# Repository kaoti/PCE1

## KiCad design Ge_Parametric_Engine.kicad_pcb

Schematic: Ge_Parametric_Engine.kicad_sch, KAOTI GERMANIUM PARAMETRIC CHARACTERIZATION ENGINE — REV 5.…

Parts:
BZ1: BUZZER_12MM; Buzzer_12mm
C1: 100uF_16V; CP_Radial_D8_P3.5mm
C2, C8, C9, C10, C11, C12, C13, C14, C15, C16, C18, C19, C20, C21, C22: 100nF; C_Disc_P5.00mm
C7, C17: 10uF_25V; CP_Radial_D8_P3.5mm
C_A0, C_A1, C_A2, C_A3: 100nF_C0G; C_Disc_P5.00mm
C_A1A, C_A2A: 100uF_16V; CP_Radial_D8_P3.5mm
C_A1B, C_A2B: 100nF; C_Disc_P5.00mm
C_ADC_FA: 10uF_16V; CP_Radial_D8_P3.5mm
C_BAT_BYP: 100uF_16V; CP_Radial_D8_P3.5mm
C_BYP_ISO1, C_BYP_ISO2: 100nF; C_Disc_P5.00mm
C_DAC1, C_DAC2: 100nF; C_Disc_P5.00mm
C_DB_BA: 100nF; C_Disc_P5.00mm
C_DB_BB: 100nF; C_Disc_P5.00mm
C_DB_DN: 100nF; C_Disc_P5.00mm
C_DB_ENCA: 10nF; C_Disc_P5.00mm
C_DB_ENCB: 10nF; C_Disc_P5.00mm
C_DB_ENCSW: 100nF; C_Disc_P5.00mm
C_DB_LF: 100nF; C_Disc_P5.00mm
C_DB_RT: 100nF; C_Disc_P5.00mm
C_DB_UP: 100nF; C_Disc_P5.00mm
C_DIG1: 100uF_16V; CP_Radial_D8_P3.5mm
C_DIG2: 100nF; C_Disc_P5.00mm
C_PI1A, C_PI2A: 100uF_35V; CP_Radial_D8_P3.5mm
C_PI1B, C_PI2B: 100nF; C_Disc_P5.00mm
C_PMID: 10uF_25V; CP_Radial_D8_P3.5mm
C_POR: 1uF; C_Disc_P5.00mm
C_RST_M11: 100nF; C_Disc_P5.00mm
C_SNUB: 10nF; C_Disc_P5.00mm
C_SYS1: 100uF_16V; CP_Radial_D8_P3.5mm
C_SYS2: 100nF; C_Disc_P5.00mm
C_TRES: 1uF; C_Disc_P5.00mm
C_USB_IN: 100nF; C_Disc_P5.00mm
D1: ANA_9V_ON; LED_D3mm_Green
D2: AFE_ACT; LED_D3mm_Blue
D_BZ: 1N4148; D_DO-35_P7.62mm
D_CH1, D_CH2, D_CH3: 1N3595; D_DO-35_P7.62mm
D_CL1, D_CL2, D_CL3: 1N3595; D_DO-35_P7.62mm
D_HVH: 1N3595; D_DO-35_P7.62mm
D_HVL: 1N3595; D_DO-35_P7.62mm
D_LED1: 1_PWR_GREEN; LED_D3mm_Green
D_LED2: 2_CHG_AMBER; LED_D3mm_Yellow
D_LED3: 3_STBY_RF_CYAN; LED_D3mm_Blue
D_LED4: 4_SCAN_BLUE; LED_D3mm_Blue
D_LED5: 5_DUT_OK_GREEN; LED_D3mm_Green
D_LED6: 6_FAULT_RED; LED_D3mm_Red
D_OVP: 1N4743A_13V; D_DO-41_P10.16mm
D_TVS_USB: P6KE15A; D_DO-15_P10.16mm
ENC1: EC11_NAV_KNOB; EC11_Knob_Encoder
F1: RXEF017_170mA; Fuse_PTC_P5.00mm
F_USB: RXEF175_1.75A; Fuse_PTC_P5.00mm
JP_M1_3V3: JP_M1_3V3_ISO; Header_1x02_P2.54mm
JP_M2_3V3: JP_M2_3V3_ISO; Header_1x02_P2.54mm
J_BAT: LIPO_1S_3V7_NON_HV; Header_1x02_P2.54mm
J_CYD_UART: CYD_P1_UART_TAP; Header_1x04_P2.54mm
J_DUT3: DUT_3PIN_SKT; Socket_1x03_DUT
J_KELVIN: KELVIN_LEADS; Header_1x04_P2.54mm
J_NTC: BAT_NTC_10K; Header_1x02_P2.54mm
J_TEMP: DS18B20_TEMP; Socket_TO92_3Pin
J_TERM5: PROBE_5P_508; TerminalBlock_5Pin_508
J_USB_C: USBC_5V_3A_HVDCP; Socket_USBC_Breakout
J_ZIF: ZIF-14_DUT; Socket_ZIF_14Pin
L1: 100uH_1A; L_Radial_P5.00mm
L2: 47uH_1A; L_Radial_P5.00mm
MOD_ADS: ADS1115_16Bit; Socket_ADS1115_Module
MOD_BOOST: MT3608_14.5V; Socket_MT3608_Boost
MOD_CHG: BQ25895_NVDC_3A; Socket_BQ25895_Charger
MOD_TFT1: TFT1_1.9_IPS_CURVE; Socket_TFT_1_9_Curve
MOD_TFT2: TFT2_1.9_IPS_DMM; Socket_TFT_1_9_DMM
Q_ANA_N: 2N7000; Socket_TO92_3Pin
Q_ANA_SW: NDP6020P; TO-220-3_Vertical
Q_BLK: 2N7000; Socket_TO92_3Pin
Q_BZ: 2N3904; Socket_TO92_3Pin
Q_LIM1, Q_LIM2: 2N3906; Socket_TO92_3Pin
Q_OVC: 2N3904; Socket_TO92_3Pin
Q_REV_BAT: NDP6020P; TO-220-3_Vertical
R_ADC_F: 10R_1%; R_Axial_P7.62mm
R_ALRT: 10k; R_Axial_P7.62mm
R_BLEED_SYS: 10k; R_Axial_P7.62mm
R_BZ_B: 1.0k; R_Axial_P7.62mm
R_BZ_PD: 10k; R_Axial_P7.62mm
R_CC1, R_CC2: 5.1k_1%; R_Axial_P7.62mm
R_CYD_RX: 470R; R_Axial_P7.62mm
R_CYD_TX: 470R; R_Axial_P7.62mm
R_D1A, R_D2A, R_D3A, R_D4A: 1.50k_0.1%; R_Axial_P7.62mm
R_D1B, R_D2B, R_D3B, R_D4B: 499R_0.1%; R_Axial_P7.62mm
R_DAC1, R_DAC2: 10k; R_Axial_P7.62mm
R_DACCS: 10k; R_Axial_P7.62mm
R_DAMP1: 2.2R_0.5W; R_Axial_P7.62mm
R_DAMP2: 1.5R_0.25W; R_Axial_P7.62mm
R_DP1, R_DP2: 100k; R_Axial_P7.62mm
R_EN1, R_EN2, R_EN3: 100k; R_Axial_P7.62mm
R_ESD1, R_ESD2, R_ESD3: 10k; R_Axial_P7.62mm
R_G1A, R_G2A: 34.8k_0.1%; R_Axial_P7.62mm
R_G1B, R_G2B: 10.0k_0.1%; R_Axial_P7.62mm
R_G_ANA: 100R; R_Axial_P7.62mm
R_G_BLK: 100R; R_Axial_P7.62mm
R_G_REV: 1.0k; R_Axial_P7.62mm
R_HV1: 100k_0.1%; R_Axial_P7.62mm
R_HV2: 10.0k_0.1%; R_Axial_P7.62mm
R_IBIAS: 10k; R_Axial_P7.62mm
R_ILIM: 43R_1%; R_Axial_P7.62mm
R_ISO1, R_ISO2, R_ISO3: 10k; R_Axial_P7.62mm
R_KA1, R_KA2, R_KA3: 2.49k_0.1%; R_Axial_P7.62mm
R_KB1, R_KB2, R_KB3: 2.20M_0.1%; R_Axial_P7.62mm
R_KG1, R_KG2, R_KG3: 2.49k_0.1%; R_Axial_P7.62mm
R_LA1, R_LA2, R_LA3: 470R_0.1%; R_Axial_P7.62mm
R_LATCH_PD: 10k; R_Axial_P7.62mm
R_LED1: 3.3k; R_Axial_P7.62mm
R_LED2: 1.0k; R_Axial_P7.62mm
R_LED3, R_LED4, R_LED5, R_LED6: 470R; R_Axial_P7.62mm
R_LED_CHG: 1.5k; R_Axial_P7.62mm
R_LED_ISO1, R_LED_ISO2: 470R_1%; R_Axial_P7.62mm
R_LED_PWR: 1.0k; R_Axial_P7.62mm
R_LG1, R_LG2, R_LG3: 470R_0.1%; R_Axial_P7.62mm
R_MB1, R_MB2, R_MB3: 100k_0.1%; R_Axial_P7.62mm
R_OEN: 10k; R_Axial_P7.62mm
R_OVC_DIV1: 100k; R_Axial_P7.62mm
R_OVC_DIV2: 22k; R_Axial_P7.62mm
R_PD1, R_PD2, R_PD3: 100k; R_Axial_P7.62mm
R_PD_ANA: 100k; R_Axial_P7.62mm
R_PD_BLK: 100k; R_Axial_P7.62mm
R_POR: 10k; R_Axial_P7.62mm
R_PR1, R_PR2, R_PR3: 100R_0.5W_0.1%; R_Axial_P7.62mm
R_PU_BA: 10k; R_Axial_P7.62mm
R_PU_BB: 10k; R_Axial_P7.62mm
R_PU_DN: 10k; R_Axial_P7.62mm
R_PU_ENCA: 10k; R_Axial_P7.62mm
R_PU_ENCB: 10k; R_Axial_P7.62mm
R_PU_ENCSW: 10k; R_Axial_P7.62mm
R_PU_ISO1, R_PU_ISO2: 2.2k; R_Axial_P7.62mm
R_PU_LF: 10k; R_Axial_P7.62mm
R_PU_OVC: 10k; R_Axial_P7.62mm
R_PU_RT: 10k; R_Axial_P7.62mm
R_PU_STBY: 10k; R_Axial_P7.62mm
R_PU_SW: 47k; R_Axial_P7.62mm
R_PU_UP: 10k; R_Axial_P7.62mm
R_RST_M11: 10k; R_Axial_P7.62mm
R_SCL: 4.7k; R_Axial_P7.62mm
R_SDA: 4.7k; R_Axial_P7.62mm
R_SNUB: 100R; R_Axial_P7.62mm
R_STAR: 0R_STAR_BRIDGE; Star_Bridge_0R
R_T1CS, R_T2CS: 10k; R_Axial_P7.62mm
R_TEMP: 4.7k; R_Axial_P7.62mm
R_TRES: 10k; R_Axial_P7.62mm
R_UI_SCL: 4.7k; R_Axial_P7.62mm
R_UI_SDA: 4.7k; R_Axial_P7.62mm
SW_A: BTN_A_SCAN; SW_Tact_12mm_Red
SW_B: BTN_B_BACK; SW_Tact_12mm_Blue
SW_BZ: MUTE_SWITCH; SW_Slide_SPDT_THT
SW_DOWN: DPAD_DOWN; SW_Tact_12mm_Yellow
SW_LEFT: DPAD_LEFT; SW_Tact_12mm_Yellow
SW_PWR: MASTER_PWR_DPDT_3A; SW_Slide_DPDT_THT
SW_RIGHT: DPAD_RIGHT; SW_Tact_12mm_Yellow
SW_STBY: STANDBY_RF_MODE; SW_Slide_SPDT_THT
SW_UP: DPAD_UP; SW_Tact_12mm_Yellow
U1, U2, U3: DG408DJ; Socket_DIP-16_W7.62mm
U4: LMC6484IN; Socket_DIP-14_W7.62mm
U5: TLC2272ACP; Socket_DIP-8_W7.62mm
U6, U7: 74HC595N; Socket_DIP-16_W7.62mm
U8: DG412LDJ; Socket_DIP-16_W7.62mm
U9: MCP4822-E/P; Socket_DIP-8_W7.62mm
U10: DG409DJ; Socket_DIP-16_W7.62mm
U11: MCP23017-E/SP; Socket_DIP-28_W7.62mm
U_ISO1, U_ISO2: H11L1M; Socket_DIP-6_W7.62mm
U_LDO_ANA: MCP1826S-3302E/AB; TO-220-3_Vertical
U_LDO_DIG: MCP1826S-3302E/AB; TO-220-3_Vertical
U_MCU1: WEMOS_LOLIN32_Lite; Socket_Wemos_Lolin32_Lite
U_MCU2: ESP32-C3_SuperMini; Socket_ESP32_C3_SuperMini
U_REG9: L78L09ACZ; Socket_TO92_3Pin
U_REG12: L7812CV; TO-220-3_Vertical

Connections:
+3V3_ADC: C9.1, C_ADC_FA.1 (+), MOD_ADS.1 (VDD), R_ADC_F.2
+3V3_ANA: C1.1 (+), C2.1, C12.1, C13.1, C19.1, C_BYP_ISO2.1, JP_M1_3V3.1, J_TEMP.3 (VDD), R_ADC_F.1, R_ALRT.1, R_DACCS.1, R_LED_ISO1.1, R_OEN.1, R_POR.1, R_PU_ISO2.1, R_PU_OVC.1, R_SCL.1, R_SDA.1, R_TEMP.1, U6.16 (VCC), U7.16 (VCC), U8.12 (VL), U9.1 (VDD), U10.2 (EN), U_ISO2.6 (VCC), U_LDO_ANA.3 (VOUT)
+3V3_DIG: C22.1, C_BYP_ISO1.1, C_DIG1.1 (+), C_DIG2.1, JP_M2_3V3.1, MOD_TFT1.2 (VCC), MOD_TFT2.2 (VCC), R_LED_CHG.1, R_LED_ISO2.1, R_LED_PWR.1, R_PU_BA.1, R_PU_BB.1, R_PU_DN.1, R_PU_ENCA.1, R_PU_ENCB.1, R_PU_ENCSW.1, R_PU_ISO1.1, R_PU_LF.1, R_PU_RT.1, R_PU_STBY.1, R_PU_UP.1, R_RST_M11.1, R_T1CS.1, R_T2CS.1, R_TRES.1, R_UI_SCL.1, R_UI_SDA.1, SW_BZ.3 (B), U11.9 (VDD), U_ISO1.6 (VCC), U_LDO_DIG.3 (VOUT)
+9V_LIM: Q_LIM1.3 (C), R_OVC_DIV2.1, U1.9 (S8), U2.9 (S8), U3.9 (S8), U10.6 (S3A)
+9V_REF: C7.1 (+), C8.1, Q_LIM2.1 (E), R_ILIM.1, R_LED1.1, R_OVC_DIV1.1, U_REG9.1 (OUT)
+12V_A: C10.1, C11.1, C14.1, C15.1, C16.1, C17.1 (+), C18.1, C20.1, C21.1, D_CH1.1 (K), D_CH2.1 (K), D_CH3.1 (K), D_HVH.1 (K), D_OVP.1 (K), F1.2, U1.13 (V+), U2.13 (V+), U3.13 (V+), U4.4 (VDD), U5.8 (VCC), U8.13 (V+), U10.14 (V+), U_REG9.3 (IN)
ADC_CAL: C_A3.1, MOD_ADS.10 (A3), R_D4A.2, R_D4B.1
ADC_TP1: C_A0.1, MOD_ADS.7 (A0), R_D1A.2, R_D1B.1, R_ISO1.1
ADC_TP2: C_A1.1, MOD_ADS.8 (A1), R_D2A.2, R_D2B.1, R_ISO2.1
ADC_TP3: C_A2.1, MOD_ADS.9 (A2), R_D3A.2, R_D3B.1, R_ISO3.1
ADS_ALRT: MOD_ADS.6 (ALRT), R_ALRT.2, U_MCU1.4 (IO34)
AFE_SPI_MOSI: U6.14 (SER), U9.4 (SDI), U_MCU1.10 (IO27)
AFE_SPI_SCK: U6.11 (SRCLK), U7.11 (SRCLK), U9.3 (SCK), U_MCU1.11 (IO14)
AGND: C1.2 (-), C2.2, C7.2 (-), C8.2, C9.2, C10.2, C11.2, C12.2, C13.2, C14.2, C15.2, C16.2, C17.2 (-), C18.2, C19.2, C20.2, C21.2, C_A0.2, C_A1.2, C_A1A.2 (-), C_A1B.2, C_A2.2, C_A2A.2 (-), C_A2B.2, C_A3.2, C_ADC_FA.2 (-), C_BYP_ISO2.2, C_DAC1.2, C_DAC2.2, C_PI1A.2 (-), C_PI1B.2, C_PI2A.2 (-), C_PI2B.2, C_POR.2, D1.1 (K), D2.1 (K), D_CL1.2 (A), D_CL2.2 (A), D_CL3.2 (A), D_HVL.2 (A), D_OVP.2 (A), J_KELVIN.4, J_TEMP.1 (GND), J_TERM5.4 (COM), MOD_ADS.2 (GND), MOD_ADS.5 (ADDR), MOD_BOOST.2 (IN-), MOD_BOOST.4 (OUT-), Q_OVC.1 (E), R_D1B.2, R_D2B.2, R_D3B.2, R_D4B.2, R_DP1.2, R_DP2.2, R_EN1.2, R_EN2.2, R_EN3.2, R_G1B.2, R_G2B.2, R_HV2.2, R_IBIAS.2, R_KG1.2, R_KG2.2, R_KG3.2, R_LATCH_PD.2, R_LG1.2, R_LG2.2, R_LG3.2, R_PD1.2, R_PD2.2, R_PD3.2, R_STAR.2 (AGND), U1.3 (V-), U1.10 (S7), U1.14 (GND), U2.3 (V-), U2.10 (S7), U2.14 (GND), U3.3 (V-), U3.10 (S7), U3.14 (GND), U4.11 (GND), U5.4 (GND), U6.8 (GND), U7.8 (GND), U8.3 (S1), U8.4 (V-), U8.5 (GND), U8.6 (S4), U8.7 (D4), U8.8 (IN4), U8.11 (S3), U8.14 (S2), U9.5 (LDAC), U9.7 (VSS), U10.3 (V-), U10.9 (DB), U10.10 (S4B), U10.11 (S3B), U10.12 (S2B), U10.13 (S1B), U10.15 (GND), U_ISO2.5 (GND), U_LDO_ANA.2 (GND), U_MCU1.13 (GND), U_REG9.2 (GND), U_REG12.2 (GND)
ANA_I2C_SCL: MOD_ADS.3 (SCL), R_SCL.2, U_MCU1.17 (IO23/SCL)
ANA_I2C_SDA: MOD_ADS.4 (SDA), R_SDA.2, U_MCU1.16 (IO19/SDA)
ANA_PWR_EN: R_G_ANA.1, R_PD_ANA.1, U11.8 (GPB7)
BAT_NTC: J_NTC.1, MOD_CHG.6 (TS)
BTN_A: C_DB_BA.1, R_PU_BA.2, SW_A.1, U11.25 (GPA4)
BTN_B: C_DB_BB.1, R_PU_BB.2, SW_B.1, U11.26 (GPA5)
BTN_DOWN: C_DB_DN.1, R_PU_DN.2, SW_DOWN.1, U11.22 (GPA1)
BTN_LEFT: C_DB_LF.1, R_PU_LF.2, SW_LEFT.1, U11.23 (GPA2)
BTN_RIGHT: C_DB_RT.1, R_PU_RT.2, SW_RIGHT.1, U11.24 (GPA3)
BTN_UP: C_DB_UP.1, R_PU_UP.2, SW_UP.1, U11.21 (GPA0)
BUF_CAL: R_D4A.1, U4.13 (4IN-), U4.14 (4OUT)
BUF_TP1: R_D1A.1, U4.1 (1OUT), U4.2 (1IN-)
BUF_TP2: R_D2A.1, U4.6 (2IN-), U4.7 (2OUT)
BUF_TP3: R_D3A.1, U4.8 (3OUT), U4.9 (3IN-)
BZ_COL: BZ1.2 (-), C_SNUB.2, D_BZ.2 (A), Q_BZ.3 (C)
BZ_POS: BZ1.1 (+), D_BZ.1 (K), R_SNUB.1, SW_BZ.2 (COM)
BZ_PWM: R_BZ_B.1, U_MCU2.13 (GPIO3/BZ)
BZ_SNUB_MID: C_SNUB.1, R_SNUB.2
C1_S1: R_LA1.1, U1.4 (S1)
C1_S2: R_KA1.1, U1.5 (S2)
C1_S3: R_MB1.1, U1.6 (S3)
C1_S4: R_KB1.1, U1.7 (S4)
C1_S5: R_LG1.1, U1.12 (S5)
C1_S6: R_KG1.1, U1.11 (S6)
C2_S1: R_LA2.1, U2.4 (S1)
C2_S2: R_KA2.1, U2.5 (S2)
C2_S3: R_MB2.1, U2.6 (S3)
C2_S4: R_KB2.1, U2.7 (S4)
C2_S5: R_LG2.1, U2.12 (S5)
C2_S6: R_KG2.1, U2.11 (S6)
C3_S1: R_LA3.1, U3.4 (S1)
C3_S2: R_KA3.1, U3.5 (S2)
C3_S3: R_MB3.1, U3.6 (S3)
C3_S4: R_KB3.1, U3.7 (S4)
C3_S5: R_LG3.1, U3.12 (S5)
C3_S6: R_KG3.1, U3.11 (S6)
CAL_A0: U10.1 (A0), U_MCU1.6 (IO32)
CAL_A1: U10.16 (A1), U_MCU1.7 (IO33)
CAL_MUX_OUT: U4.12 (4IN+), U10.8 (DA)
CHG_STAT_N: D_LED2.1 (K), MOD_CHG.10 (STAT)
CYD_RX_TAP: J_CYD_UART.4, R_CYD_RX.2
CYD_TX_TAP: J_CYD_UART.3, R_CYD_TX.2
DAC1_FILT: C_DAC1.1, R_DAC1.2, R_DP1.1, U5.3 (1IN+)
DAC1_RAW: R_DAC1.1, U9.8 (VOUTA)
DAC2_FILT: C_DAC2.1, R_DAC2.2, R_DP2.1, U5.5 (2IN+)
DAC2_RAW: R_DAC2.1, U9.6 (VOUTB)
DAC_CS: R_DACCS.2, U9.2 (CS), U_MCU1.9 (DAC2/26)
DGND: C22.2, C_BAT_BYP.2 (-), C_BYP_ISO1.2, C_DB_BA.2, C_DB_BB.2, C_DB_DN.2, C_DB_ENCA.2, C_DB_ENCB.2, C_DB_ENCSW.2, C_DB_LF.2, C_DB_RT.2, C_DB_UP.2, C_DIG1.2 (-), C_DIG2.2, C_PMID.2 (-), C_RST_M11.2, C_SYS1.2 (-), C_SYS2.2, C_TRES.2, C_USB_IN.2, D_LED1.1 (K), D_LED3.1 (K), D_LED4.1 (K), D_LED5.1 (K), D_LED6.1 (K), D_TVS_USB.2 (A), ENC1.2 (C), ENC1.5 (S2), J_BAT.2, J_CYD_UART.2, J_NTC.2, J_USB_C.2 (GND), MOD_CHG.3 (GND), MOD_CHG.11 (CE_N), MOD_CHG.12 (OTG), MOD_TFT1.1 (GND), MOD_TFT2.1 (GND), Q_ANA_N.1 (S), Q_BLK.1 (S), Q_BZ.1 (E), R_BLEED_SYS.2, R_BZ_PD.2, R_CC1.2, R_CC2.2, R_G_REV.2, R_PD_ANA.2, R_PD_BLK.2, R_STAR.1 (DGND), SW_A.2, SW_B.2, SW_DOWN.2, SW_LEFT.2, SW_RIGHT.2, SW_STBY.1 (A), SW_UP.2, U11.10 (VSS), U11.15 (A0), U11.16 (A1), U11.17 (A2), U_ISO1.5 (GND), U_LDO_DIG.2 (GND), U_MCU2.10 (GND)
DMM_30V: J_TERM5.5 (V30V), R_HV1.1
DMM_30V_DIV: D_HVH.2 (A), D_HVL.1 (K), R_HV1.2, R_HV2.1, U10.7 (S4A)
ENC_A: C_DB_ENCA.1, ENC1.1 (A), R_PU_ENCA.2, U11.1 (GPB0)
ENC_B: C_DB_ENCB.1, ENC1.3 (B), R_PU_ENCB.2, U11.2 (GPB1)
ENC_SW: C_DB_ENCSW.1, ENC1.4 (S1), R_PU_ENCSW.2, U11.27 (GPA6)
ESD_TP1: R_ESD1.2, U4.3 (1IN+)
ESD_TP2: R_ESD2.2, U4.5 (2IN+)
ESD_TP3: R_ESD3.2, U4.10 (3IN+)
FAST_TP1: R_ISO1.2, U_MCU1.1 (VP/36)
FAST_TP2: R_ISO2.2, U_MCU1.2 (VN/39)
FAST_TP3: R_ISO3.2, U_MCU1.5 (IO35)
FAULT_OVC_N: Q_OVC.3 (C), R_PU_OVC.2, U_MCU1.8 (DAC1/25)
FB_SRCA: R_G1A.2, R_G1B.1, U5.2 (1IN-)
FB_SRCB: R_G2A.2, R_G2B.1, U5.6 (2IN-)
ISO1_A: R_LED_ISO1.2, U_ISO1.1 (A)
ISO2_A: R_LED_ISO2.2, U_ISO2.1 (A)
J_BAT+: J_BAT.1, SW_PWR.2 (COM1)
LED1_A: D1.2 (A), R_LED1.2
LED2_A: D2.2 (A), R_LED2.2
LED2_DRV: R_LED2.1, U7.7 (QH)
LED3_A: D_LED3.2 (A), R_LED3.2
LED4_A: D_LED4.2 (A), R_LED4.2
LED5_A: D_LED5.2 (A), R_LED5.2
LED6_A: D_LED6.2 (A), R_LED6.2
LED_CHG_A: D_LED2.2 (A), R_LED_CHG.2
LED_DUT_OK: R_LED5.1, U11.5 (GPB4)
LED_FAULT: R_LED6.1, U11.6 (GPB5)
LED_PWR_A: D_LED1.2 (A), R_LED_PWR.2
LED_SCAN: R_LED4.1, U11.4 (GPB3)
LED_STBY_RF: R_LED3.1, U11.3 (GPB2)
LIM_BASE: Q_LIM1.2 (B), Q_LIM2.3 (C), R_IBIAS.1
LIM_SENSE: Q_LIM1.1 (E), Q_LIM2.2 (B), R_ILIM.2
LINK_RX_M1: R_PU_ISO2.2, U_ISO2.4 (VO), U_MCU1.26 (IO13)
LINK_RX_M2: R_CYD_RX.1, R_PU_ISO1.2, U_ISO1.4 (VO), U_MCU2.7 (GPIO20/RX)
LINK_TX_M1: U_ISO1.2 (K), U_MCU1.21 (IO16)
LINK_TX_M2: R_CYD_TX.1, U_ISO2.2 (K), U_MCU2.8 (GPIO21/TX)
M1_3V3: JP_M1_3V3.2, U_MCU1.14 (3V3)
M2_3V3: JP_M2_3V3.2, U_MCU2.11 (3V3)
MCP_RST_N: C_RST_M11.1, R_RST_M11.2, U11.18 (RESET)
PMID_BYP: C_PMID.1 (+), MOD_CHG.2 (PMID)
Q_ANA_NG: Q_ANA_N.2 (G), R_G_ANA.2
Q_ANA_SW_G: Q_ANA_N.3 (D), Q_ANA_SW.1 (G), R_PU_SW.2
Q_BLK_G: Q_BLK.2 (G), R_G_BLK.2
Q_BZ_B: Q_BZ.2 (B), R_BZ_B.2, R_BZ_PD.1
Q_OVC_B: Q_OVC.2 (B), R_OVC_DIV1.2, R_OVC_DIV2.2
Q_REV_G: Q_REV_BAT.1 (G), R_G_REV.1
SR_CHAIN: U6.9 (QH'), U7.14 (SER)
SR_CLR_N: C_POR.1, R_POR.2, U6.10 (SRCLR), U7.10 (SRCLR)
SR_LATCH: R_LATCH_PD.1, U6.12 (RCLK), U7.12 (RCLK), U_MCU1.18 (IO18)
SR_OE_N: R_OEN.2, U6.13 (OE_N), U7.13 (OE_N), U_MCU1.20 (IO17)
SW_G1: R_PD1.1, U7.4 (QE), U8.1 (IN1)
SW_G2: R_PD2.1, U7.5 (QF), U8.16 (IN2)
SW_G3: R_PD3.1, U7.6 (QG), U8.9 (IN3)
SW_STBY: R_PU_STBY.2, SW_STBY.2 (COM), U11.28 (GPA7)
TEMP_DQ: J_TEMP.2 (DQ), R_TEMP.2, U_MCU1.22 (IO4)
TFT1_CS: MOD_TFT1.7 (CS), R_T1CS.2, U_MCU2.3 (GPIO7/CS1)
TFT2_CS: MOD_TFT2.7 (CS), R_T2CS.2, U_MCU2.6 (GPIO10/CS2)
TFT_BLK: MOD_TFT1.8 (BLK), MOD_TFT2.8 (BLK), Q_BLK.3 (D)
TFT_BLK_EN: R_G_BLK.1, R_PD_BLK.1, U11.7 (GPB6)
TFT_DC: MOD_TFT1.6 (DC), MOD_TFT2.6 (DC), U_MCU2.1 (GPIO5/DC)
TFT_RES: C_TRES.1, MOD_TFT1.5 (RES), MOD_TFT2.5 (RES), R_TRES.2
TP1_DUT: J_DUT3.1, J_KELVIN.1, J_TERM5.1 (TP1), J_ZIF.1, J_ZIF.2, J_ZIF.3, J_ZIF.12, J_ZIF.13, J_ZIF.14, R_ESD1.1, R_PR1.1
TP1_MUX: D_CH1.2 (A), D_CL1.1 (K), R_PR1.2, U1.8 (D_COM), U8.2 (D1)
TP2_DUT: J_DUT3.2, J_KELVIN.2, J_TERM5.2 (TP2), J_ZIF.4, J_ZIF.11, R_ESD2.1, R_PR2.1
TP2_MUX: D_CH2.2 (A), D_CL2.1 (K), R_PR2.2, U2.8 (D_COM), U8.15 (D2)
TP3_DUT: J_DUT3.3, J_KELVIN.3, J_TERM5.3 (TP3), J_ZIF.5, J_ZIF.6, J_ZIF.7, J_ZIF.8, J_ZIF.9, J_ZIF.10, R_ESD3.1, R_PR3.1
TP3_MUX: D_CH3.2 (A), D_CL3.1 (K), R_PR3.2, U3.8 (D_COM), U8.10 (D3)
U1_A0: U1.1 (A0), U6.15 (QA)
U1_A1: U1.16 (A1), U6.1 (QB)
U1_A2: U1.15 (A2), U6.2 (QC)
U1_EN: R_EN1.1, U1.2 (EN), U6.3 (QD)
U2_A0: U2.1 (A0), U6.4 (QE)
U2_A1: U2.16 (A1), U6.5 (QF)
U2_A2: U2.15 (A2), U6.6 (QG)
U2_EN: R_EN2.1, U2.2 (EN), U6.7 (QH)
U3_A0: U3.1 (A0), U7.15 (QA)
U3_A1: U3.16 (A1), U7.1 (QB)
U3_A2: U3.15 (A2), U7.2 (QC)
U3_EN: R_EN3.1, U3.2 (EN), U7.3 (QD)
UI_I2C_SCL: MOD_CHG.7 (SCL), R_UI_SCL.2, U11.12 (SCL), U_MCU2.15 (GPIO1/SCL)
UI_I2C_SDA: MOD_CHG.8 (SDA), R_UI_SDA.2, U11.13 (SDA), U_MCU2.16 (GPIO0/SDA)
UI_SPI_MOSI: MOD_TFT1.4 (SDA), MOD_TFT2.4 (SDA), U_MCU2.2 (GPIO6/MOSI)
UI_SPI_SCK: MOD_TFT1.3 (SCL), MOD_TFT2.3 (SCL), U_MCU2.12 (GPIO4/SCK)
USB_CC1: J_USB_C.3 (CC1), R_CC1.1
USB_CC2: J_USB_C.4 (CC2), R_CC2.1
V_3V3_FILT: C_A2A.1 (+), C_A2B.1, R_DAMP2.2, U_LDO_ANA.1 (VIN)
V_12V_PRE: F1.1, U_REG12.3 (OUT)
V_14V_FILT: C_PI2A.1 (+), C_PI2B.1, R_DAMP1.2, U_REG12.1 (IN)
V_ANA_IN: C_A1A.1 (+), C_A1B.1, L2.1, MOD_BOOST.1 (IN+), Q_ANA_SW.2 (D)
V_BAT_PROT: C_BAT_BYP.1 (+), MOD_CHG.5 (BAT), Q_REV_BAT.3 (S)
V_BAT_SW: Q_REV_BAT.2 (D), SW_PWR.3 (ON1)
V_BOOST_RAW: C_PI1A.1 (+), C_PI1B.1, L1.1, MOD_BOOST.3 (OUT+)
V_BUS_SYS: C_SYS1.1 (+), C_SYS2.1, J_CYD_UART.1, Q_ANA_SW.3 (S), R_PU_SW.1, SW_PWR.6 (ON2), U_LDO_DIG.1 (VIN)
V_LC1_MID: L1.2, R_DAMP1.1
V_LC2_MID: L2.2, R_DAMP2.1
V_SRC_A: R_G1A.1, R_KA1.2, R_KA2.2, R_KA3.2, R_LA1.2, R_LA2.2, R_LA3.2, U5.1 (1OUT), U10.4 (S1A)
V_SRC_B: R_G2A.1, R_KB1.2, R_KB2.2, R_KB3.2, R_MB1.2, R_MB2.2, R_MB3.2, U5.7 (2OUT), U10.5 (S2A)
V_SYS_BLEED: R_BLEED_SYS.1, SW_PWR.4 (OFF2)
V_SYS_RAW: MOD_CHG.4 (SYS), SW_PWR.5 (COM2)
V_USB_PROT: C_USB_IN.1, D_TVS_USB.1 (K), F_USB.2, MOD_CHG.1 (VBUS)
V_USB_RAW: F_USB.1, J_USB_C.1 (VBUS)

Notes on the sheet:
1. POWER, 3.7V NON-HV LIPO PROTECTION & TI BQ25895 1.5MHz NVDC FAST-CHARGER
2. SWITCHABLE ANALOG RAIL, 2x CRITICALLY DAMPED LC PI-FILTERS, LDOs & 15mA LIMITER
3. MCU 1 QUIET ANALOG CORE (LOLIN32 LITE) & 2x H11L1M OPTO-ISOLATED UART
4. MCU 2 COMMS/UI/AUDIO CORE (ESP32-C3 SUPERMINI) & U11 MCP23017 EXPANDER
5. SOLID-STATE 3-TERMINAL AFE MATRIX (74HC595N, 3x DG408DJ, DG412LDJ) & FAILSAFES
6. ADS1115 16-BIT ADC, MCP4822 DAC, TLC2272ACP, LMC6484IN 20fA BUFFER & DG409DJ
7. DUAL 1.9in ST7789 IPS DISPLAYS, BACKLIGHT SWITCH & RETRO D-PAD / ENCODER
8. TOP 6-LED STATUS BAR & 56K MODEM BUZZER STAGE (MUTE SWITCH & RC SNUBBER)

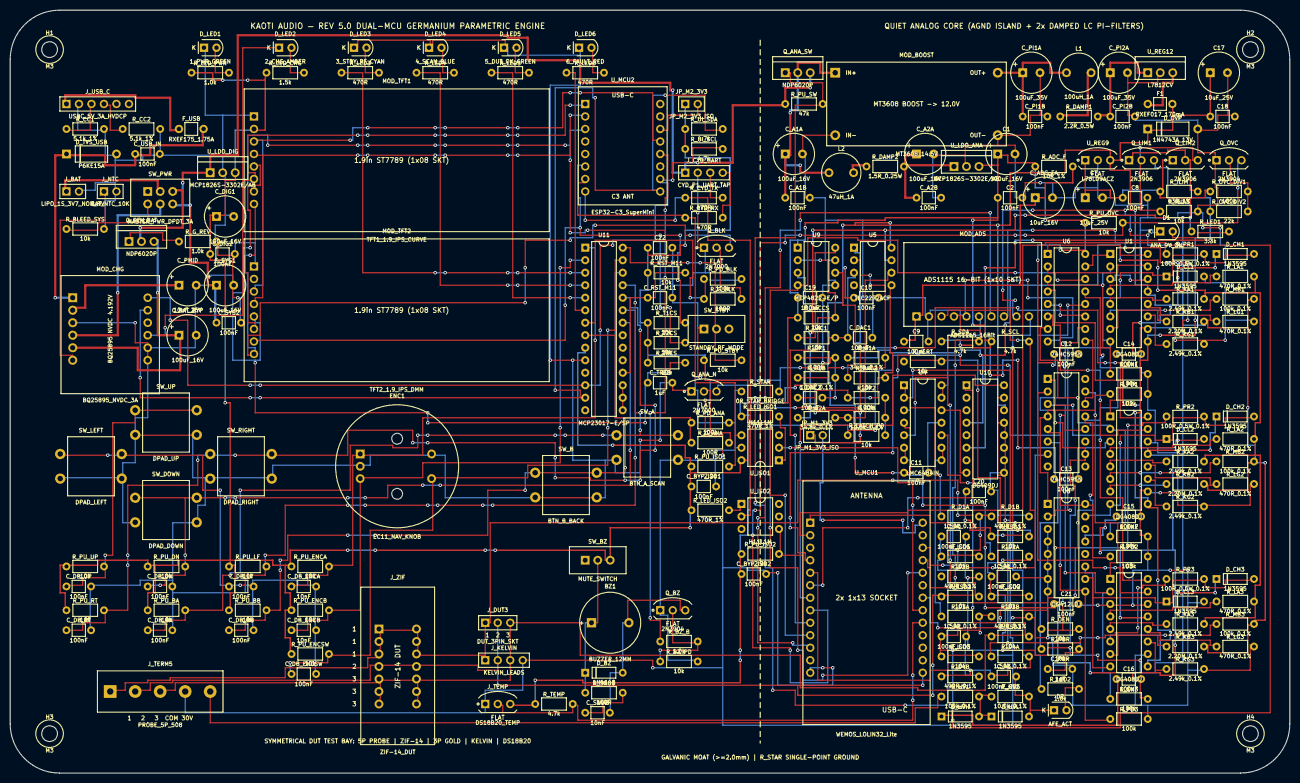
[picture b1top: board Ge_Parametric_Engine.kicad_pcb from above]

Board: 2 copper layers, 260.0 x 155.0 mm, 246 parts (0 on the bottom side), 163 nets.

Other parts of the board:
H1, H2, H3, H4: M3; MountingHole_M3

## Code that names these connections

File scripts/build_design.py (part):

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    add("D_BZ",    "D_THT",       "1N4148",      "D_DO-35_P7.62mm",   {1: "BZ_POS", 2: "BZ_COL"}, block=8)
    add("R_SNUB",  "R_THT",       "100R",        "R_Axial_P7.62mm",   {1: "BZ_POS", 2: "BZ_SNUB_MID"}, block=8)
    add("C_SNUB",  "C_THT",       "10nF",        "C_Disc_P5.00mm",    {1: "BZ_SNUB_MID", 2: "BZ_COL"}, block=8)
    add("Q_BZ",    "NPN_2N3904",  "2N3904",      "Socket_TO92_3Pin",  {1: "DGND", 2: "Q_BZ_B", 3: "BZ_COL"}, block=8)
    add("R_BZ_B",  "R_THT",       "1.0k",        "R_Axial_P7.62mm",   {1: "BZ_PWM", 2: "Q_BZ_B"}, block=8)
    add("R_BZ_PD", "R_THT",       "10k",         "R_Axial_P7.62mm",   {1: "Q_BZ_B", 2: "DGND"}, block=8)

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
    # ==================== 3. GALVANIC ISOLATION BOUNDARY (X = 152.40 mm: DGND <-> AGND) ====================
    # U_ISO1 & U_ISO2 straddle the X = 152.40 mm moat, and R_STAR bridges DGND (left) to AGND (right)!
    pos["R_STAR"]       = (148.59, 77.47, 0)   # Pin 1 (148.59, DGND) -> Pin 2 (156.21, AGND)
    pos["Q_ANA_N"]      = (138.43, 77.47, 0)   # In DGND zone driving Q_ANA_SW gate
    pos["R_PD_ANA"]     = (138.43, 83.82, 0)
    pos["R_G_ANA"]      = (138.43, 87.88, 0)

    pos["U_ISO1"]       = (156.21, 91.44, 180) # Rotated 180 so Pin 1..3 (AGND side) are at X=156.21, Pin 4..6 (DGND) at X=148.59!
    pos["R_LED_ISO1"]   = (148.59, 82.55, 0)
    pos["R_PU_ISO1"]    = (138.43, 92.71, 0)
    pos["C_BYP_ISO1"]   = (138.43, 96.77, 0)

    pos["U_ISO2"]       = (148.59, 100.33, 0)  # Pin 1..3 (DGND side) at X=148.59, Pin 4..6 (AGND) at X=156.21!
    pos["R_LED_ISO2"]   = (138.43, 101.60, 0)
    pos["R_PU_ISO2"]    = (148.59, 110.49, 0)
    pos["C_BYP_ISO2"]   = (148.59, 114.55, 0)
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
